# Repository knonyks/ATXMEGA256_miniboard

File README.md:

# ONYKS ATXMEGA256 Miniboard
Miniboard to prosta płytka deweloperska stworzona dla mikrokontrolera ATXMEGA256 przez KN ONYKS. Płytka zawiera możliwie minimalną liczbę elementów potrzebnych do zaczęcia programowania tego mikrokontrolera aby użytkownik miał pełną kontrolę nad swoim projektem.

<br>
<br>

## TODO

- [x] Schemat połączeń MCU
- [x] Schemat sekcji zasilania
- [x] PCB
- [x] Dokumentacja - schematy, PCB, zdjęcia
- [ ] Dokumentacja - instrukcja obsługi
- [x] Dokumentacja - BOM
- [ ] Toolchain
- [x] Modele 3D
- [ ] Rysunek techniczny (poglądowy)

## Autorzy
Szymon Bartosik, Mateusz Turycz

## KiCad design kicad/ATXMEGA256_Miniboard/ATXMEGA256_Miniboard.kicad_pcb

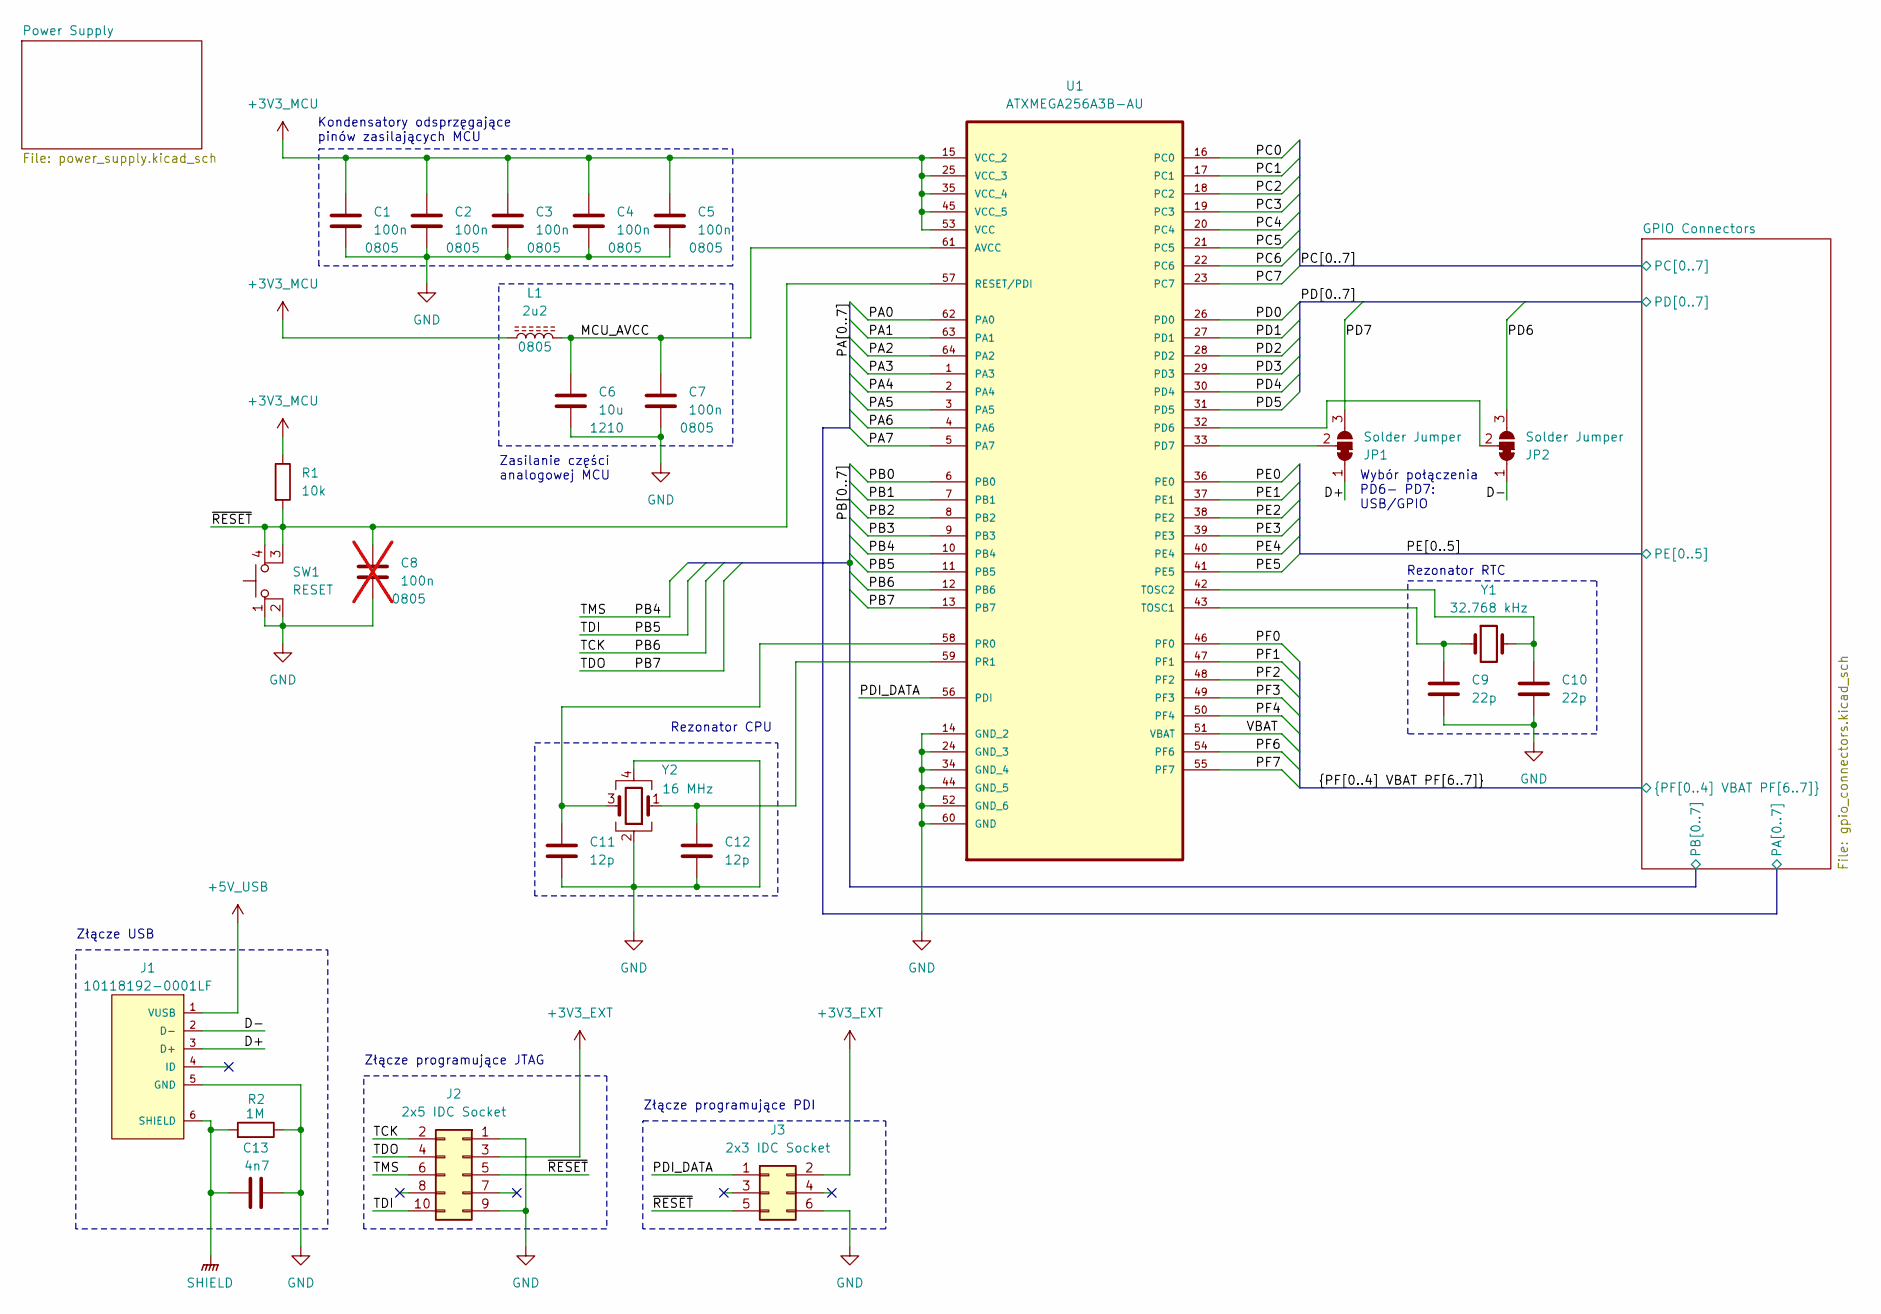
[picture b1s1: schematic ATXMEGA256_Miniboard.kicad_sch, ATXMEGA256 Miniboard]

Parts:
C1, C2, C3, C4, C5, C7: 100n; C_0805_2012Metric_Pad1.18x1.45mm_HandSolder; Part Number C0805C104J4RACTU
C6: 10u; C_1210_3225Metric_Pad1.33x2.70mm_HandSolder; Part Number C1210C106K4RAC
C8: 100n; C_0805_2012Metric_Pad1.18x1.45mm_HandSolder; Part Number C0805C104J4RACTU; not fitted
C9, C10: 22p; C_0603_1608Metric_Pad1.08x0.95mm_HandSolder; Part Number C0603C220J5GAC7867
C11, C12: 12p; C_0603_1608Metric_Pad1.08x0.95mm_HandSolder; Part Number C0603C120J5GACTU
C13: 4n7; C_0603_1608Metric_Pad1.08x0.95mm_HandSolder; Part Number C0603C472K3RACTU
J1: 10118192-0001LF; AMPHENOL_10118192-0001LF; Part Number 10118192-0001LF
J2: 2x5 IDC Socket; IDC-Header_2x05_P2.54mm_Vertical; Part Number DS1013-10SSIB1-B-0
J3: 2x3 IDC Socket; IDC-Header_2x03_P2.54mm_Vertical; Part Number T821106A1S100CEU
JP1, JP2: Solder Jumper; SolderJumper-3_P1.3mm_Bridged12_RoundedPad1.0x1.5mm_NumberL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
L1: 2u2; L_0805_2012Metric_Pad1.15x1.40mm_HandSolder; Part Number MLZ2012A2R2WT000
R1: 10k; R_0603_1608Metric_Pad0.98x0.95mm_HandSolder; Part Number 0603SAJ0103T5E
R2: 1M; R_0603_1608Metric_Pad0.98x0.95mm_HandSolder; Part Number 0603SAJ0105T5E
SW1: RESET; SW_SMD_2-1437565-8_4_4.50_6.00_6.00_5.00; Part Number FSM2JSMAA
U1: ATXMEGA256A3B-AU; QFP80P1600X1600X120-64N; Part Number ATXMEGA256A3B-AU
Y1: 32.768 kHz; LFXTAL025159Reel; Part Number LFXTAL025159
Y2: 16 MHz; Crystal_SMD_3225-4Pin_3.2x2.5mm; Part Number LFXTAL053426

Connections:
+3V3_EXT: J2.3, J3.2; also elsewhere on the board
+3V3_MCU: C1.2, C2.2, C3.2, C4.2, C5.2, L1.1, R1.1, U1.15 (VCC_2), U1.25 (VCC_3), U1.35 (VCC_4), U1.45 (VCC_5), U1.53 (VCC); also elsewhere on the board
+5V_USB: J1.1 (VUSB); also elsewhere on the board
/D+: J1.3 (D+), JP1.1 (A)
/D-: J1.2 (D-), JP2.1 (A)
/MCU_AVCC: C6.2, C7.2, L1.2, U1.61 (AVCC)
/PA0: U1.62 (PA0); also elsewhere on the board
/PA1: U1.63 (PA1); also elsewhere on the board
/PA2: U1.64 (PA2); also elsewhere on the board
/PA3: U1.1 (PA3); also elsewhere on the board
/PA4: U1.2 (PA4); also elsewhere on the board
/PA5: U1.3 (PA5); also elsewhere on the board
/PA6: U1.4 (PA6); also elsewhere on the board
/PA7: U1.5 (PA7); also elsewhere on the board
/PB0: U1.6 (PB0); also elsewhere on the board
/PB1: U1.7 (PB1); also elsewhere on the board
/PB2: U1.8 (PB2); also elsewhere on the board
/PB3: U1.9 (PB3); also elsewhere on the board
/PB4: J2.6, U1.10 (PB4); also elsewhere on the board
/PB5: J2.10, U1.11 (PB5); also elsewhere on the board
/PB6: J2.2, U1.12 (PB6); also elsewhere on the board
/PB7: J2.4, U1.13 (PB7); also elsewhere on the board
/PC0: U1.16 (PC0); also elsewhere on the board
/PC1: U1.17 (PC1); also elsewhere on the board
/PC2: U1.18 (PC2); also elsewhere on the board
/PC3: U1.19 (PC3); also elsewhere on the board
/PC4: U1.20 (PC4); also elsewhere on the board
/PC5: U1.21 (PC5); also elsewhere on the board
/PC6: U1.22 (PC6); also elsewhere on the board
/PC7: U1.23 (PC7); also elsewhere on the board
/PD0: U1.26 (PD0); also elsewhere on the board
/PD1: U1.27 (PD1); also elsewhere on the board
/PD2: U1.28 (PD2); also elsewhere on the board
/PD3: U1.29 (PD3); also elsewhere on the board
/PD4: U1.30 (PD4); also elsewhere on the board
/PD5: U1.31 (PD5); also elsewhere on the board
/PD6: JP2.3 (B); also elsewhere on the board
/PD7: JP1.3 (B); also elsewhere on the board
/PDI_DATA: J3.1, U1.56 (PDI)
/PE0: U1.36 (PE0); also elsewhere on the board
/PE1: U1.37 (PE1); also elsewhere on the board
/PE2: U1.38 (PE2); also elsewhere on the board
/PE3: U1.39 (PE3); also elsewhere on the board
/PE4: U1.40 (PE4); also elsewhere on the board
/PE5: U1.41 (PE5); also elsewhere on the board
/PF0: U1.46 (PF0); also elsewhere on the board
/PF1: U1.47 (PF1); also elsewhere on the board
/PF2: U1.48 (PF2); also elsewhere on the board
/PF3: U1.49 (PF3); also elsewhere on the board
/PF4: U1.50 (PF4); also elsewhere on the board
/PF6: U1.54 (PF6); also elsewhere on the board
/PF7: U1.55 (PF7); also elsewhere on the board
/VBAT: U1.51 (VBAT); also elsewhere on the board
/~RESET: C8.2, J2.5, J3.5, R1.2, SW1.3 (K), SW1.4 (A), U1.57 (RESET/PDI)
GND: C1.1, C2.1, C3.1, C4.1, C5.1, C6.1, C7.1, C8.1, C9.1, C10.1, C11.1, C12.1, C13.1, J1.5 (GND), J2.1, J2.9, J3.6, R2.1, SW1.1, SW1.2, U1.14 (GND_2), U1.24 (GND_3), U1.34 (GND_4), U1.44 (GND_5), U1.52 (GND_6), U1.60 (GND), Y2.2, Y2.4; also elsewhere on the board
unnamed: JP1.2 (C), U1.33 (PD7)
unnamed: JP2.2 (C), U1.32 (PD6)
unnamed: C11.2, U1.58 (PR0), Y2.3
unnamed: C12.2, U1.59 (PR1), Y2.1
unnamed: C9.2, U1.43 (TOSC1), Y1.1
unnamed: C10.2, U1.42 (TOSC2), Y1.2
SHIELD: C13.2, J1.6 (SHIELD), R2.2

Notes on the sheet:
Kondensatory odsprzęgające pinów zasilających MCU
Złącze USB
Zasilanie części analogowej MCU
Złącze programujące PDI
Złącze programujące JTAG
Wybór połączenia PD6- PD7: USB/GPIO
Rezonator RTC
Rezonator CPU

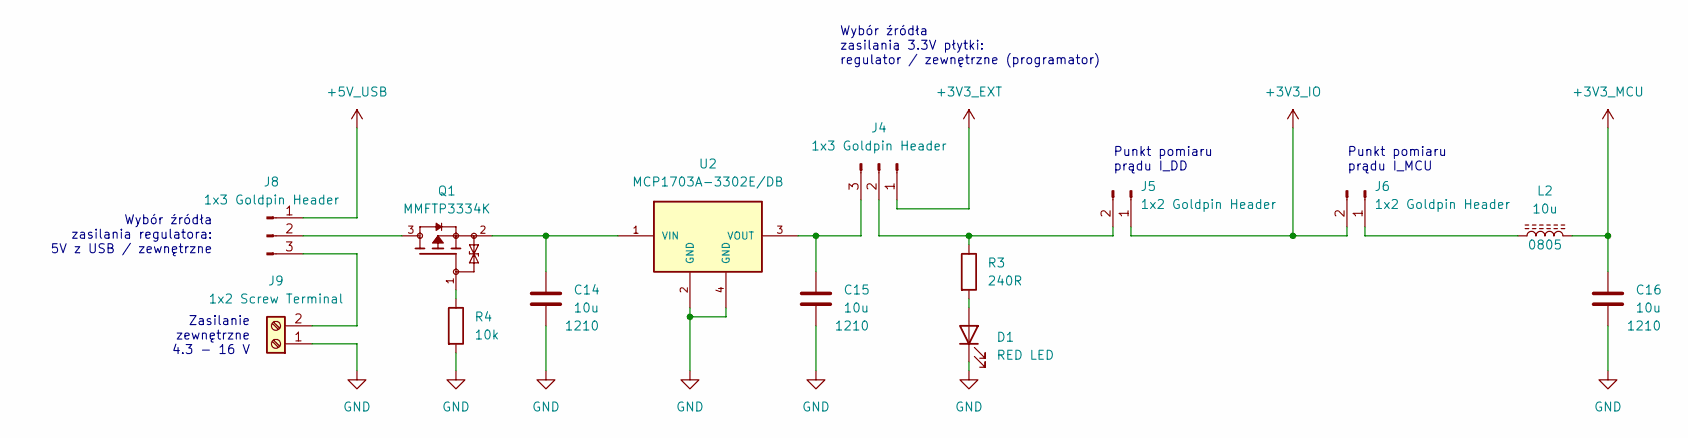
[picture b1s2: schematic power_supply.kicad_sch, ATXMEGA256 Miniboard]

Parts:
C14, C15, C16: 10u; C_1210_3225Metric_Pad1.33x2.70mm_HandSolder; Part Number C1210C106K4RAC
D1: RED LED; LED_0805_2012Metric_Pad1.15x1.40mm_HandSolder; Part Number LTST-C171KRKT
J4, J8: 1x3 Goldpin Header; PinHeader_1x03_P2.54mm_Vertical; Part Number DS1021-1X3SF182-B
J5, J6: 1x2 Goldpin Header; PinHeader_1x02_P2.54mm_Vertical; Part Number DS1021-1X2SF162-B
J9: 1x2 Screw Terminal; DG381-3.5-02P-13-00AH; Part Number DG381-3.5-02P-13-00AH
L2: 10u; L_0805_2012Metric_Pad1.05x1.20mm_HandSolder; Part Number MLZ2012M100HT000
Q1: MMFTP3334K; TRANS_MMFTP3334K; Part Number MMFTP3334K
R3: 240R; R_0805_2012Metric_Pad1.20x1.40mm_HandSolder; Part Number 0805S8J0241T5E
R4: 10k; R_0603_1608Metric_Pad0.98x0.95mm_HandSolder; Part Number 0603SAJ0103T5E
U2: MCP1703A-3302E/DB; SOT230P700X180-4N; Part Number MCP1703A-3302E/DB

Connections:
+3V3_EXT: J4.1; also elsewhere on the board
+3V3_IO: J5.1, J6.2; also elsewhere on the board
+3V3_MCU: C16.2, L2.2; also elsewhere on the board
+5V_USB: J8.1; also elsewhere on the board
GND: C14.1, C15.1, C16.1, D1.1 (K), J9.1, R4.2, U2.2 (GND), U2.4 (GND); also elsewhere on the board
unnamed: D1.2 (A), R3.2
unnamed: J4.2, J5.2, R3.1
unnamed: C15.2, J4.3, U2.3 (VOUT)
unnamed: J6.1, L2.1
unnamed: J8.2, Q1.3
unnamed: J8.3, J9.2
unnamed: Q1.1, R4.1
unnamed: C14.2, Q1.2, U2.1 (VIN)

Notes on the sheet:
Punkt pomiaru prądu I_MCU
Punkt pomiaru prądu I_DD
Wybór źródła zasilania regulatora: 5V z USB / zewnętrzne
Wybór źródła zasilania 3.3V płytki: regulator / zewnętrzne (programator)
Zasilanie zewnętrzne 4.3 - 16 V

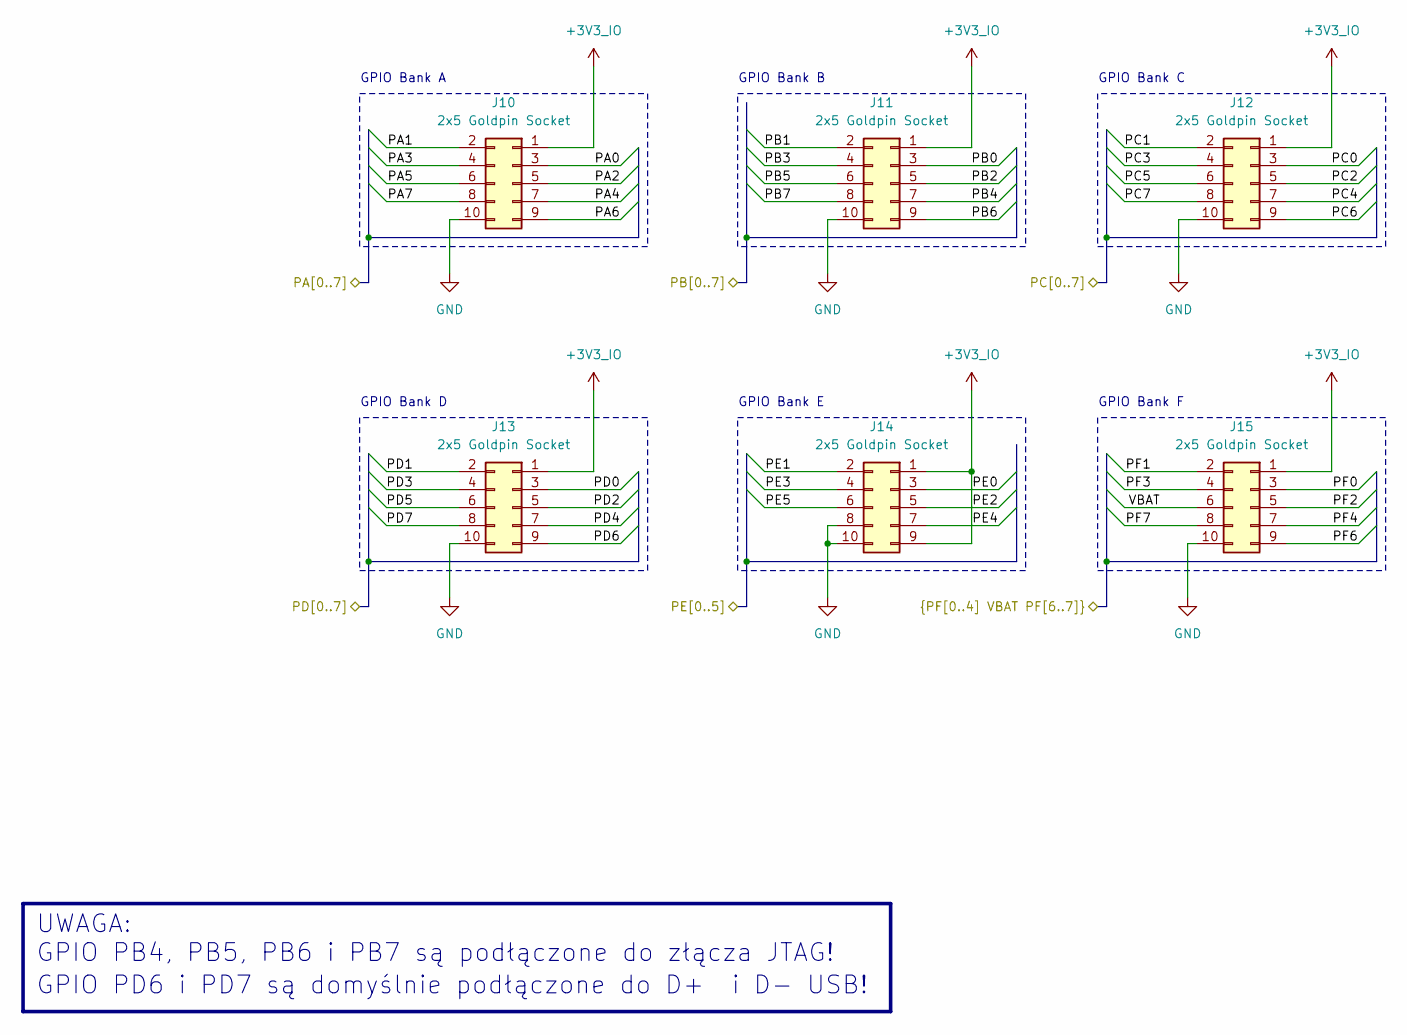
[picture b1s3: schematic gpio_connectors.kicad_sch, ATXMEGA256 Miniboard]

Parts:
J10, J11, J12, J13, J14, J15: 2x5 Goldpin Socket; PinSocket_2x05_P2.54mm_Vertical_SMD; Part Number ZL264-10DG

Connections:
+3V3_IO: J10.1, J11.1, J12.1, J13.1, J14.1, J14.9, J15.1; also elsewhere on the board
/PA0: J10.3; also elsewhere on the board
/PA1: J10.2; also elsewhere on the board
/PA2: J10.5; also elsewhere on the board
/PA3: J10.4; also elsewhere on the board
/PA4: J10.7; also elsewhere on the board
/PA5: J10.6; also elsewhere on the board
/PA6: J10.9; also elsewhere on the board
/PA7: J10.8; also elsewhere on the board
/PB0: J11.3; also elsewhere on the board
/PB1: J11.2; also elsewhere on the board
/PB2: J11.5; also elsewhere on the board
/PB3: J11.4; also elsewhere on the board
/PB4: J11.7; also elsewhere on the board
/PB5: J11.6; also elsewhere on the board
/PB6: J11.9; also elsewhere on the board
/PB7: J11.8; also elsewhere on the board
/PC0: J12.3; also elsewhere on the board
/PC1: J12.2; also elsewhere on the board
/PC2: J12.5; also elsewhere on the board
/PC3: J12.4; also elsewhere on the board
/PC4: J12.7; also elsewhere on the board
/PC5: J12.6; also elsewhere on the board
/PC6: J12.9; also elsewhere on the board
/PC7: J12.8; also elsewhere on the board
/PD0: J13.3; also elsewhere on the board
/PD1: J13.2; also elsewhere on the board
/PD2: J13.5; also elsewhere on the board
/PD3: J13.4; also elsewhere on the board
/PD4: J13.7; also elsewhere on the board
/PD5: J13.6; also elsewhere on the board
/PD6: J13.9; also elsewhere on the board
/PD7: J13.8; also elsewhere on the board
/PE0: J14.3; also elsewhere on the board
/PE1: J14.2; also elsewhere on the board
/PE2: J14.5; also elsewhere on the board
/PE3: J14.4; also elsewhere on the board
/PE4: J14.7; also elsewhere on the board
/PE5: J14.6; also elsewhere on the board
/PF0: J15.3; also elsewhere on the board
/PF1: J15.2; also elsewhere on the board
/PF2: J15.5; also elsewhere on the board
/PF3: J15.4; also elsewhere on the board
/PF4: J15.7; also elsewhere on the board
/PF6: J15.9; also elsewhere on the board
/PF7: J15.8; also elsewhere on the board
/VBAT: J15.6; also elsewhere on the board
GND: J10.10, J11.10, J12.10, J13.10, J14.8, J14.10, J15.10; also elsewhere on the board

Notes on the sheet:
GPIO Bank E
GPIO Bank F
GPIO Bank B
GPIO Bank D
GPIO PD6 i PD7 są domyślnie podłączone do D+ i D- USB!
GPIO PB4, PB5, PB6 i PB7 są podłączone do złącza JTAG!
UWAGA:
GPIO Bank A
GPIO Bank C

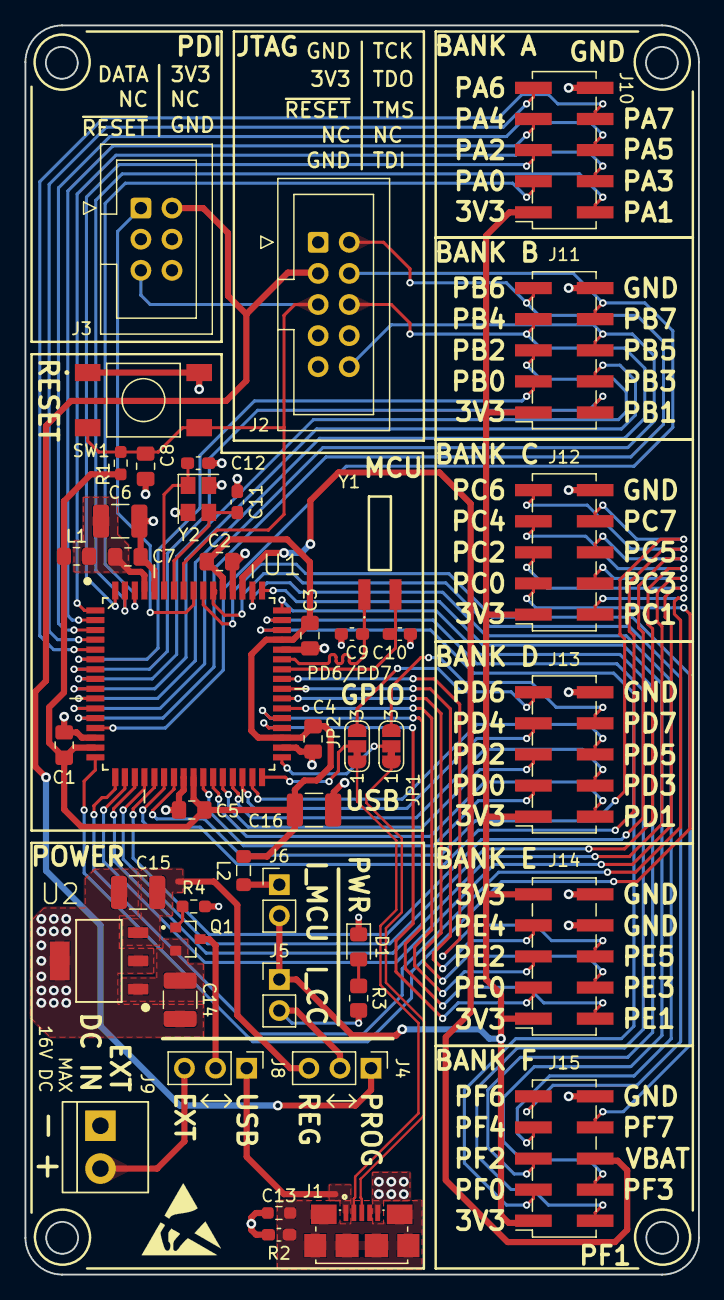
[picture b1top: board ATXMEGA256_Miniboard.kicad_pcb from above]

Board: 4 copper layers, 55.0 x 102.0 mm, 45 parts (0 on the bottom side), 71 nets.

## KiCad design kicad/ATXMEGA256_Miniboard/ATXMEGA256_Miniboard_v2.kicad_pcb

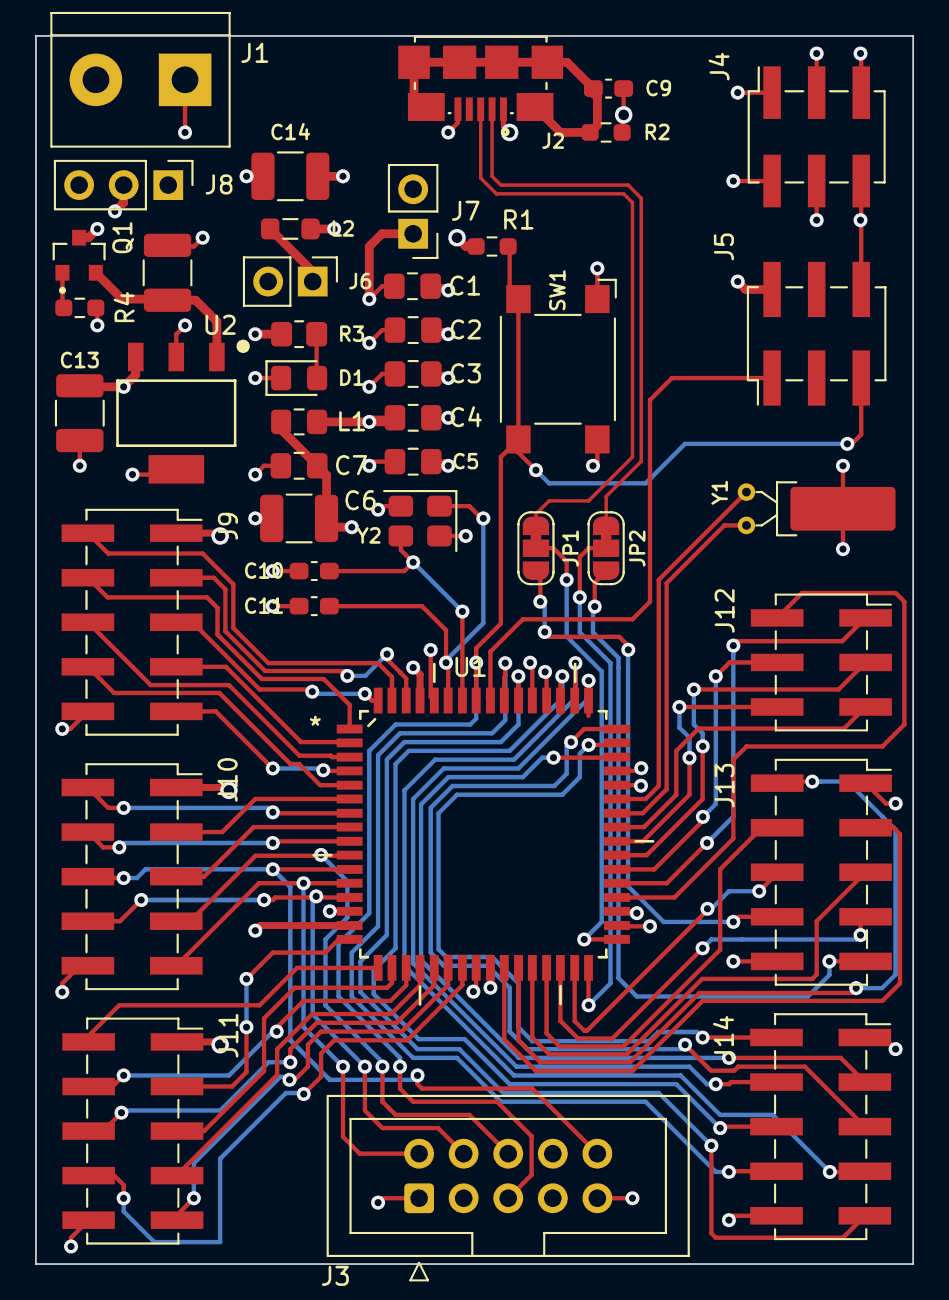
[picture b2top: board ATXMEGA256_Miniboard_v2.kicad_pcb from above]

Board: 4 copper layers, 50.0 x 70.0 mm, 42 parts (0 on the bottom side), 69 nets.

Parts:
C1, C2, C3, C4, C5, C7: 100n; C_0805_2012Metric_Pad1.18x1.45mm_HandSolder
C6, C12, C13, C14: 10u; C_1210_3225Metric_Pad1.33x2.70mm_HandSolder
C9: 4n7; C_0603_1608Metric_Pad1.08x0.95mm_HandSolder
C10, C11: 12p; C_0603_1608Metric_Pad1.08x0.95mm_HandSolder
D1: RED LED; LED_0805_2012Metric_Pad1.15x1.40mm_HandSolder
J1: 1x2 Screw Terminal; TerminalBlock_bornier-2_P5.08mm
J2: 10118192-0001LF; AMPHENOL_10118192-0001LF
J3: 2x5 IDC Socket; IDC-Header_2x05_P2.54mm_Vertical
J4, J12: 2x3 Goldpin Socket; PinSocket_2x03_P2.54mm_Vertical_SMD
J5: 2x3 Goldpin Header; PinHeader_2x03_P2.54mm_Vertical_SMD
J6, J7: 1x2 Goldpin Header; PinHeader_1x02_P2.54mm_Vertical
J8: 1x3 Goldpin Header; PinHeader_1x03_P2.54mm_Vertical
J9, J10, J11, J13, J14: 2x5 Goldpin Socket; PinSocket_2x05_P2.54mm_Vertical_SMD
JP1, JP2: Solder Jumper; SolderJumper-3_P1.3mm_Bridged12_RoundedPad1.0x1.5mm_NumberL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
L1: 2u2; L_0805_2012Metric_Pad1.15x1.40mm_HandSolder
L2: 10u; L_0805_2012Metric_Pad1.05x1.20mm_HandSolder
Q1: MMFTP3334K; TRANS_MMFTP3334K
R1, R4: 10k; R_0603_1608Metric_Pad0.98x0.95mm_HandSolder
R2: 1M; R_0603_1608Metric_Pad0.98x0.95mm_HandSolder
R3: 240R; R_0805_2012Metric_Pad1.20x1.40mm_HandSolder
SW1: RESET; SW_SPST_Omron_B3FS-100xP
U1: ATXMEGA256A3B-AU; QFP80P1600X1600X120-64N
U2: MCP1703A-3302E/DB; SOT230P700X180-4N
Y1: 32.768 kHz; Crystal_DS26_D2.0mm_L6.0mm_Horizontal_1EP_style1
Y2: 16 MHz; Crystal_SMD_3225-4Pin_3.2x2.5mm

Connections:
+3V3: C13.2, J3.3, J5.2, J6.2, J9.1, J10.1, J11.1, J13.1, J14.1, R3.1, U2.3 (VOUT)
+5V: J2.1 (VUSB), J8.1
/D+: J2.3 (D+), JP1.1 (A)
/D-: J2.2 (D-), JP2.1 (A)
/PA0: J9.3, U1.62 (PA0)
/PA1: J9.2, U1.63 (PA1)
/PA2: J9.5, U1.64 (PA2)
/PA3: J9.4, U1.1 (PA3)
/PA4: J9.7, U1.2 (PA4)
/PA5: J9.6, U1.3 (PA5)
/PA6: J9.9, U1.4 (PA6)
/PA7: J9.8, U1.5 (PA7)
/PB0: J10.3, U1.6 (PB0)
/PB1: J10.2, U1.7 (PB1)
/PB2: J10.5, U1.8 (PB2)
/PB3: J10.4, U1.9 (PB3)
/PB4: J3.6, J10.7, U1.10 (PB4)
/PB5: J3.10, J10.6, U1.11 (PB5)
/PB6: J3.2, J10.9, U1.12 (PB6)
/PB7: J3.4, J10.8, U1.13 (PB7)
/PC0: J11.3, U1.16 (PC0)
/PC1: J11.2, U1.17 (PC1)
/PC2: J11.5, U1.18 (PC2)
/PC3: J11.4, U1.19 (PC3)
/PC4: J11.7, U1.20 (PC4)
/PC5: J11.6, U1.21 (PC5)
/PC6: J11.9, U1.22 (PC6)
/PC7: J11.8, U1.23 (PC7)
/PD0: J13.3, U1.26 (PD0)
/PD1: J13.2, U1.27 (PD1)
/PD2: J13.5, U1.28 (PD2)
/PD3: J13.4, U1.29 (PD3)
/PD4: J13.7, U1.30 (PD4)
/PD5: J13.6, U1.31 (PD5)
/PD6: J13.9, JP2.3 (B)
/PD7: J13.8, JP1.3 (B)
/PDI_DATA: J5.1, U1.56 (PDI)
/PE0: J12.2, U1.36 (PE0)
/PE1: J12.1, U1.37 (PE1)
/PE2: J12.4, U1.38 (PE2)
/PE3: J12.3, U1.39 (PE3)
/PE4: J12.6, U1.40 (PE4)
/PE5: J12.5, U1.41 (PE5)
/PF0: J14.3, U1.46 (PF0)
/PF1: J14.2, U1.47 (PF1)
/PF2: J14.5, U1.48 (PF2)
/PF3: J14.4, U1.49 (PF3)
/PF4: J14.7, U1.50 (PF4)
/PF6: J14.9, U1.54 (PF6)
/PF7: J14.8, U1.55 (PF7)
/Power Supply/VCC_EXT: J1.2, J8.3
/Power Supply/VCC_MCU: C1.2, C2.2, C3.2, C4.2, C5.2, J7.1, L1.1, R1.1, U1.15 (VCC_2), U1.25 (VCC_3), U1.35 (VCC_4), U1.45 (VCC_5), U1.53 (VCC)
/VBAT: J14.6, U1.51 (VBAT)
/~RESET: J3.5, J5.5, R1.2, SW1.2, U1.57 (RESET/PDI)
GND: C1.1, C2.1, C3.1, C4.1, C5.1, C6.1, C7.1, C9.1, C10.1, C11.1, C12.1, C13.1, C14.1, D1.1 (K), J1.1, J2.5 (GND), J3.1, J3.9, J4.1, J4.2, J4.3, J4.4, J4.5, J4.6, J5.6, J9.10, J10.10, J11.10, J13.10, J14.10, R2.2, R4.2, SW1.1, U1.14 (GND_2), U1.24 (GND_3), U1.34 (GND_4), U1.44 (GND_5), U1.52 (GND_6), U1.60 (GND), U2.2 (GND), U2.4 (GND), Y1.3, Y2.2, Y2.4
unnamed: D1.2 (A), R3.2
unnamed: C9.2, J2.6 (SHIELD), R2.1
unnamed: J6.1, L2.1
unnamed: C14.2, J7.2, L2.2
unnamed: J8.2, Q1.3
unnamed: JP1.2 (C), U1.33 (PD7)
unnamed: JP2.2 (C), U1.32 (PD6)
unnamed: Q1.1, R4.1
unnamed: C6.2, C7.2, L1.2, U1.61 (AVCC)
unnamed: C10.2, U1.58 (PR0), Y2.3
unnamed: C11.2, U1.59 (PR1), Y2.1
unnamed: U1.43 (TOSC1), Y1.2
unnamed: U1.42 (TOSC2), Y1.1
unnamed: C12.2, Q1.2, U2.1 (VIN)

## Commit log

2024-03-16 pushing the project to github for the first time
2024-03-16 layout done poorly, but at least somewhat done
2024-03-17 fixed ground planes, ready for review
2024-03-17 changed headers, fixed ground planes
2024-03-17 Janusz chcial 0.5mm niepotrzebnejk sciezki
2024-03-17 done fixes after first review
2024-03-19 printing file
2024-03-19 quick fix, better pdf
2024-03-19 made smaller via holes as markers
2024-03-19 gnd fix, and 3v3 connection fix
2024-03-19 small gnd changes
2024-03-19 fixed Janusz's fixes
2024-03-19 it works now, plz dont touch it anymore
2024-03-19 output options
2024-03-19 changed tht connector hole sizes
2024-03-20 juz jest dobrze, nie ruszac
2024-05-24 fixed ldo footprint
2025-03-19 reboot
2025-03-19 test
2025-03-20 magistrale
2025-03-20 pierwsza wersja bez nazw i footprintów
2025-03-20 gotowe połączenia oprócz JTAG i kwarców
2025-03-20 v1.0
2025-03-20 poprawka TODO
2025-03-20 Create LICENSE
2025-03-20 poprawka ścieżek do bibliteki
2025-03-22 Your commit message here
2025-03-22 deleting flash module
2025-03-22 usb + udokumentowanie elementów
2025-03-22 poprawka nazwy headera
2025-03-22 deleting altium remains :(
2025-03-22 przycisk zmieniony na smd
2025-03-27 zasilanie
2025-03-27 led + złącze masy + złącze śrubowe (do opisania)
2025-03-29 poprawka estetyczna zasilania
2025-03-29 dorobiony tranzsytor zabezpieczajacy i dlawik
2025-03-30 schemat rev. 1.0
2025-04-01 optymalizacja BOM + pdf schematu
2025-04-06 aktualizacja zlacza usb
2025-04-19 rev 1.1
2025-04-23 Poprawiony schemat + sprawdzić czy nie są potrzebne kondensatory przy oscylatorze
2025-05-13 pdated parts on PCB from schematic, migrated to kicad 9
2025-05-25 PCB layout
2025-06-26 Poprawki zasilania, zmiana oscylatora RTC, poprawki polaczen GPIO
2025-07-01 Zmiana zlacza PDI, dodany makefile i struktura plikow
2025-07-16 layout komponentów
2025-07-19 wstepne poczenia
2025-07-27 layout rev 0.9, zegar do poprawy
2025-07-28 review: rerouting Power i USB
2025-07-29 PCB Rev 1.0 + obrazki
2025-07-29 update BOM, poprawki masy
2025-08-23 Kicad v.9.99 + poprawa polaryzacji na silkscreen + dokumentacja PCB
2025-08-31 dokumentacja HW
2025-12-19 poprawka define w c_cpp_properties + przykładowy kod main.c
